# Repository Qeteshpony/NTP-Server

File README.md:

# NTP-Server

[Hardware Documentation](https://qeteshpony.github.io/NTP-Server)

Raspberry Pi Hat to connect a GT-U7 GPS Module and a DS3231 RTC in an orderly fashion

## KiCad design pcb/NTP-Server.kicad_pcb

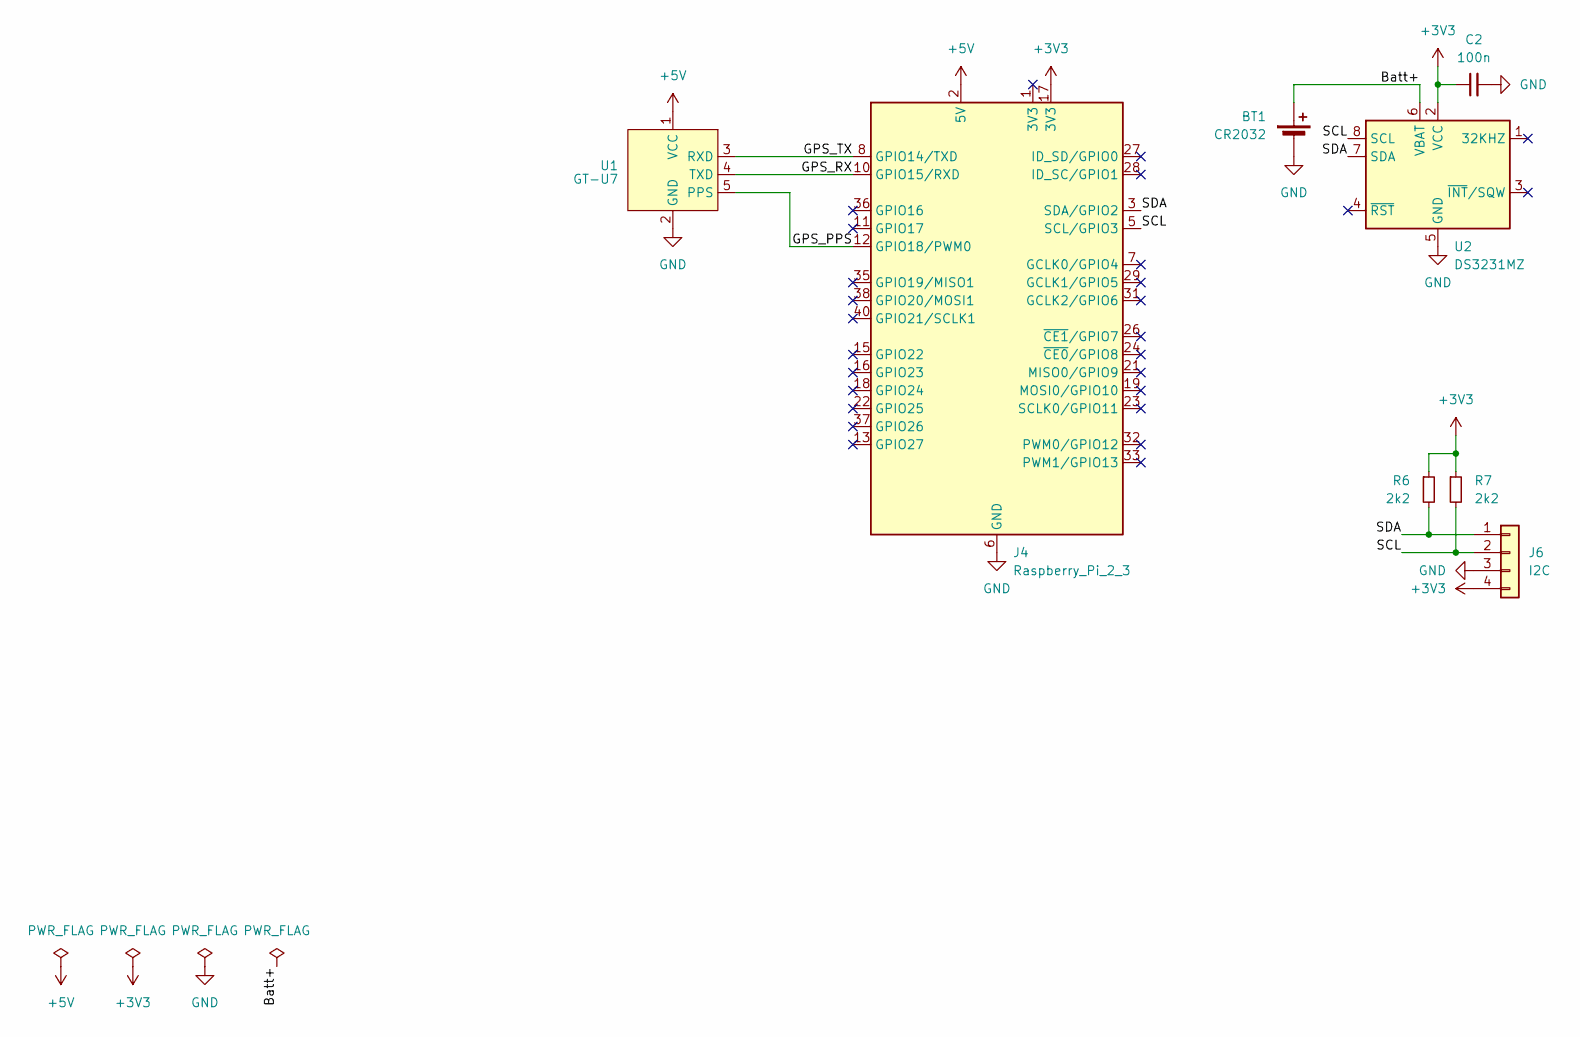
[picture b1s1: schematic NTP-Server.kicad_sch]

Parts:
BT1: CR2032; Molex_PicoBlade_53047-0210_1x02_P1.25mm_Vertical
C2: 100n; C_0603_1608Metric_Pad1.08x0.95mm_HandSolder
J4: Raspberry_Pi_2_3; PinSocket_2x20_P2.54mm_Vertical
J6: I2C; JST_PH_B4B-PH-K_1x04_P2.00mm_Vertical
R6, R7: 2k2; R_0603_1608Metric_Pad0.98x0.95mm_HandSolder
U1: GT-U7; GT-U7_SMT
U2: DS3231MZ; SOIC-8_3.9x4.9mm_P1.27mm

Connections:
+3V3: C2.1, J4.17 (3V3), J6.4, R6.1, R7.1, U2.2 (VCC)
+5V: J4.2 (5V), J4.4 (5V), U1.1 (VCC)
/Batt+: BT1.1 (+), U2.6 (VBAT)
/GPS_PPS: J4.12 (GPIO18/PWM0), U1.5 (PPS)
/GPS_RX: J4.10 (GPIO15/RXD), U1.4 (TXD)
/GPS_TX: J4.8 (GPIO14/TXD), U1.3 (RXD)
/SCL: J4.5 (SCL/GPIO3), J6.2, R7.2, U2.8 (SCL)
/SDA: J4.3 (SDA/GPIO2), J6.1, R6.2, U2.7 (SDA)
GND: BT1.2 (-), C2.2, J4.6 (GND), J4.9 (GND), J4.14 (GND), J4.20 (GND), J4.25 (GND), J4.30 (GND), J4.34 (GND), J4.39 (GND), J6.3, U1.2 (GND), U2.5 (GND)

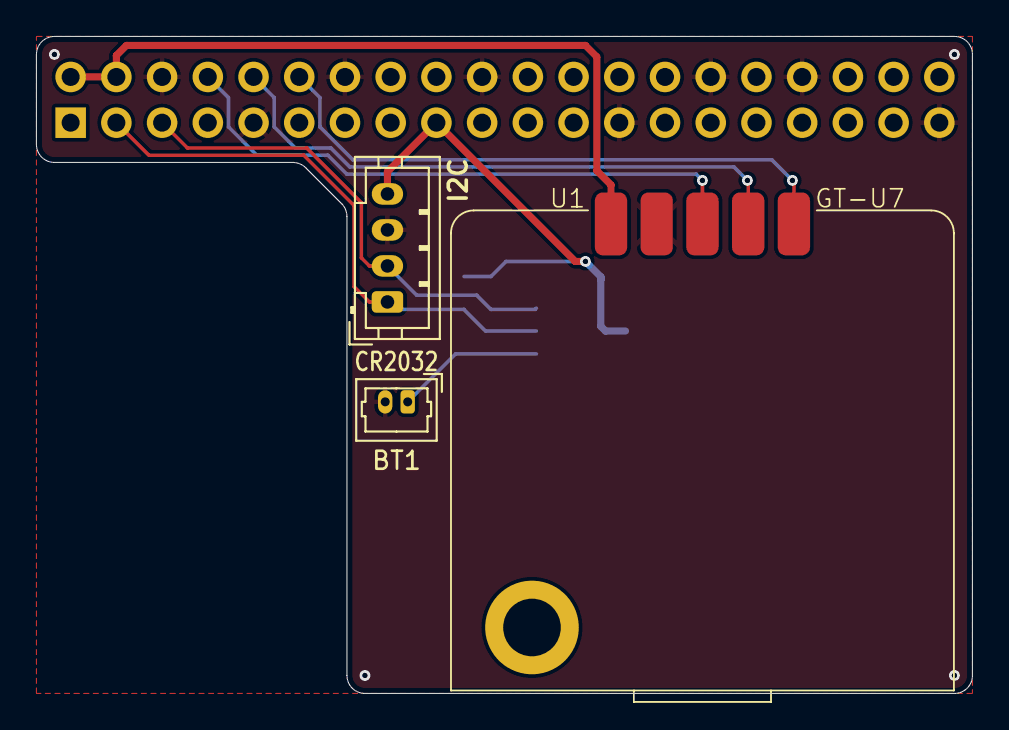
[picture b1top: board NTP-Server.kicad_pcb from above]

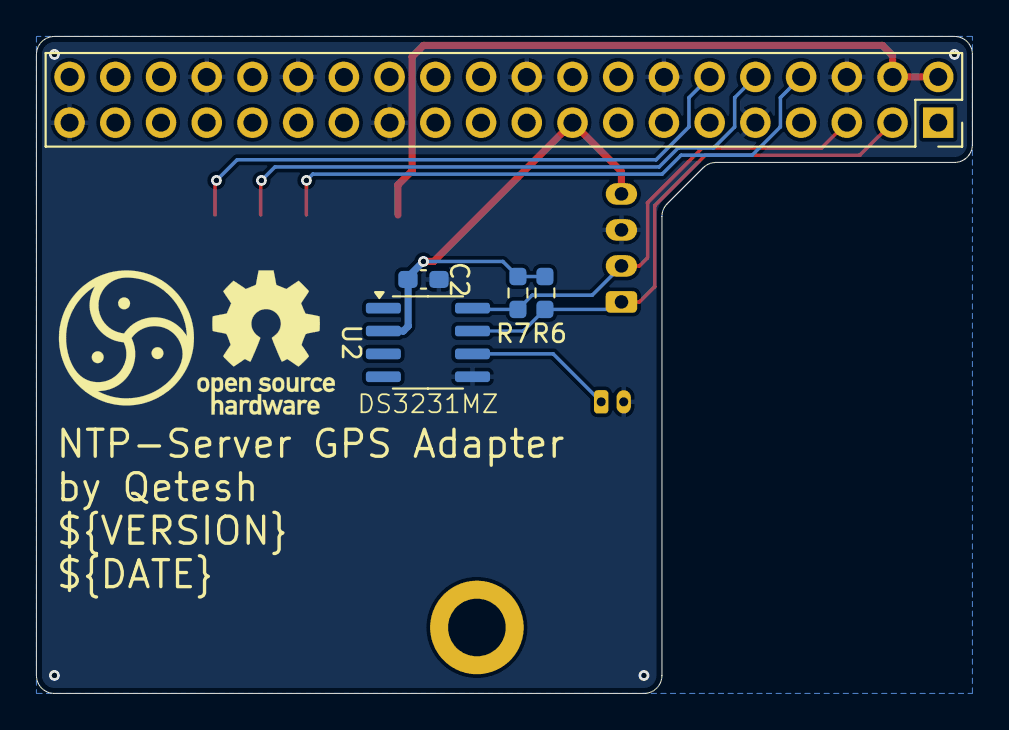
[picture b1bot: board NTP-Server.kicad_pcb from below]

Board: 2 copper layers, 52.0 x 36.5 mm, 8 parts (5 on the bottom side), 9 nets.

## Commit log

2024-07-28 feat: initial commit
2024-07-28 chore(main): release 1.0.0
2024-07-30 fix: grid origin
2024-07-30 chore(main): release 1.0.1
2024-08-29 ci: remove dependency between jobs
2024-10-26 feat!: complete redesign
    Remove unneeded parts and make the whole board a lot smaller
2024-10-26 docs: update readme
2024-10-26 ci: update kibot
2024-10-26 docs: add bottom render
2024-10-26 chore(main): release 2.0.0
